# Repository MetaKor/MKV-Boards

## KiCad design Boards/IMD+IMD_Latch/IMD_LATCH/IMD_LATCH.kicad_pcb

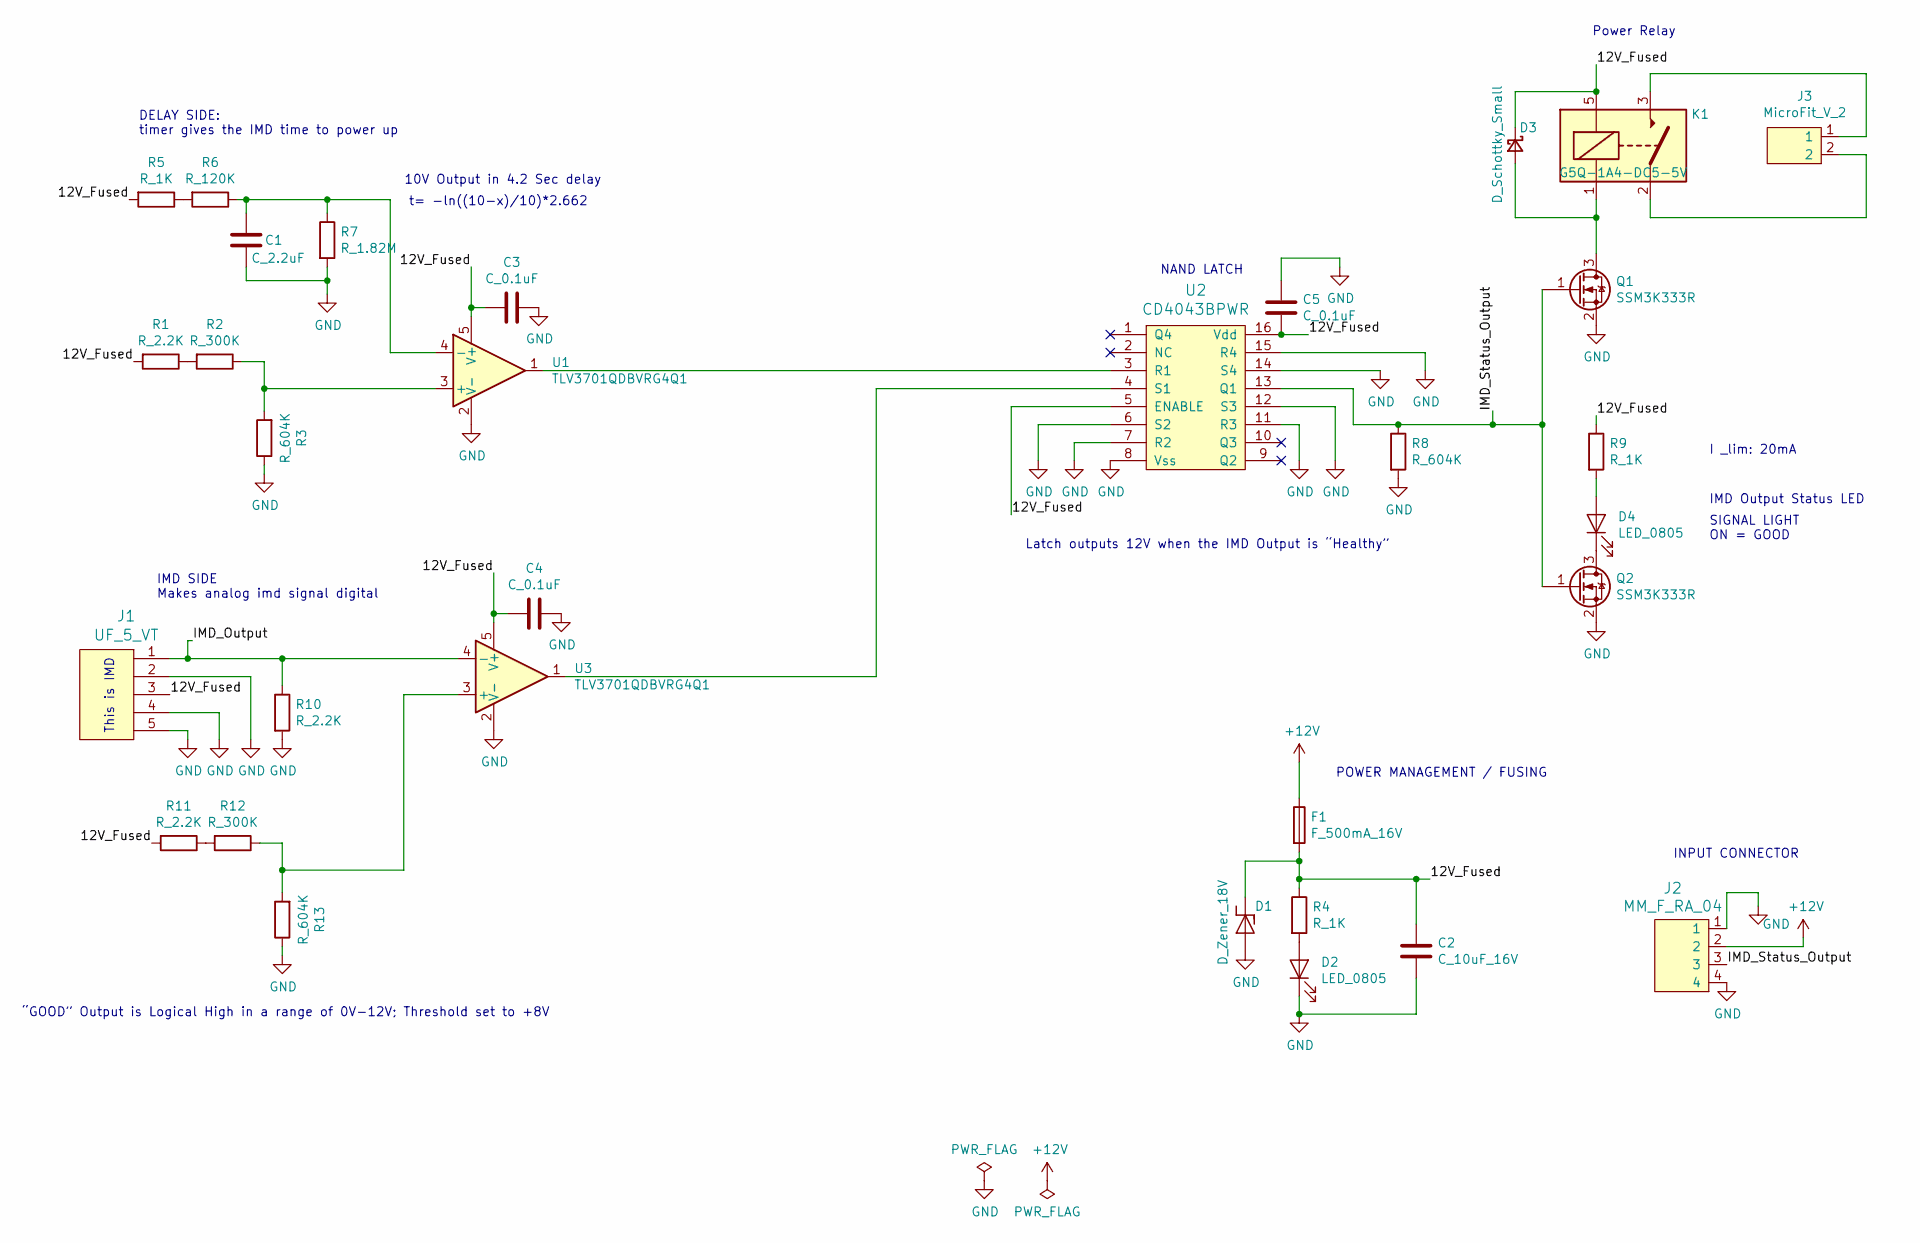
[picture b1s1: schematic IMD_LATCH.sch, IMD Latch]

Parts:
C1: C_2.2uF; C_0603_1608Metric; MPN 311-1451-1-ND
C2: C_10uF_16V; C_0805_OEM; MPN 1276-2399-1-ND
C3, C4, C5: C_0.1uF; C_0805_OEM; MPN 478-3352-1-ND
D1: D_Zener_18V; DO-214AA; MPN SMBJ5355B-TPMSCT-ND
D2, D4: LED_0805; LED_0805_OEM; MPN 475-1410-1-ND
D3: D_Schottky_Small; D_0805_OEM
F1: F_500mA_16V; Fuse_1210; MPN 507-1786-1-ND
J1: UF_5_VT; Ultrafit_5; MPN WM11667-ND
J2: MM_F_RA_04; micromatch_female_ra_4; MPN 338070-4
J3: MicroFit_V_2; MPN WM10660-ND
K1: G5Q-1A4-DC5-5V; Relay_SPST_OMRON-G5Q-1A4_OEM; MPN Z3632-ND
Q1, Q2: SSM3K333R; SOT-23F; MPN SSM3K333RLFCT-ND
R1, R10, R11: R_2.2K; R_0805_OEM; MPN RMCF0805FT2K20CT-ND
R2, R12: R_300K; R_0805_OEM; MPN P300KDACT-ND
R3, R8, R13: R_604K; R_0805_OEM; MPN RMCF0805FT604KCT-ND
R4, R5, R9: R_1K; R_0805_OEM; MPN RNCP0805FTD1K00CT-ND
R6: R_120K; R_0805_OEM; MPN RMCF0805FT120KCT-ND
R7: R_1.82M; R_0805_OEM; MPN RMCF0805FT1M82CT-ND
U1, U3: TLV3701QDBVRG4Q1; SOT-23-5_OEM; MPN 497-10249-1-ND
U2: CD4043BPWR; TSSOP-16-OEM; MPN 296-14106-1-ND

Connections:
+12V: F1.1, J2.2
/12V_Fused: C2.1, C3.2, C4.2, C5.2, D1.1 (K), D3.1 (K), F1.2, J1.3, K1.5, R1.2, R4.1, R5.2, R9.1, R11.2, U1.5 (V+), U2.5 (ENABLE), U2.16 (Vdd), U3.5 (V+)
/IMD_Output: J1.1, R10.1, U3.4 (-)
/IMD_Status_Output: J2.3, Q1.1 (G), Q2.1 (G), R8.1, U2.13 (Q1)
GND: C1.2, C2.2, C3.1, C4.1, C5.1, D1.2 (A), D2.1 (K), J1.2, J1.4, J1.5, J2.1, J2.4, Q1.2 (S), Q2.2 (S), R3.1, R7.2, R8.2, R10.2, R13.1, U1.2 (V-), U2.6 (S2), U2.7 (R2), U2.8 (Vss), U2.11 (R3), U2.12 (S3), U2.14 (S4), U2.15 (R4), U3.2 (V-)
unnamed: C1.1, R6.1, R7.1, U1.4 (-)
unnamed: D2.2 (A), R4.2
unnamed: D3.2 (A), K1.1, Q1.3 (D)
unnamed: D4.1 (K), Q2.3 (D)
unnamed: D4.2 (A), R9.2
unnamed: J3.1, K1.3
unnamed: J3.2, K1.2
unnamed: R1.1, R2.2
unnamed: R2.1, R3.2, U1.3 (+)
unnamed: R5.1, R6.2
unnamed: R11.1, R12.2
unnamed: R12.1, R13.2, U3.3 (+)
unnamed: U1.1, U2.3 (R1)
unnamed: U2.4 (S1), U3.1

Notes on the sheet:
IMD SIDE Makes analog imd signal digital
“GOOD” Output is Logical High in a range of 0V-12V; Threshold set to +8V
INPUT CONNECTOR
NAND LATCH
Power Relay
10V Output in 4.2 Sec delay
t= -ln((10-x)/10)*2.662
DELAY SIDE: timer gives the IMD time to power up
This is IMD
Latch outputs 12V when the IMD Output is “Healthy”
POWER MANAGEMENT / FUSING
SIGNAL LIGHT ON = GOOD
I _lim: 20mA
IMD Output Status LED

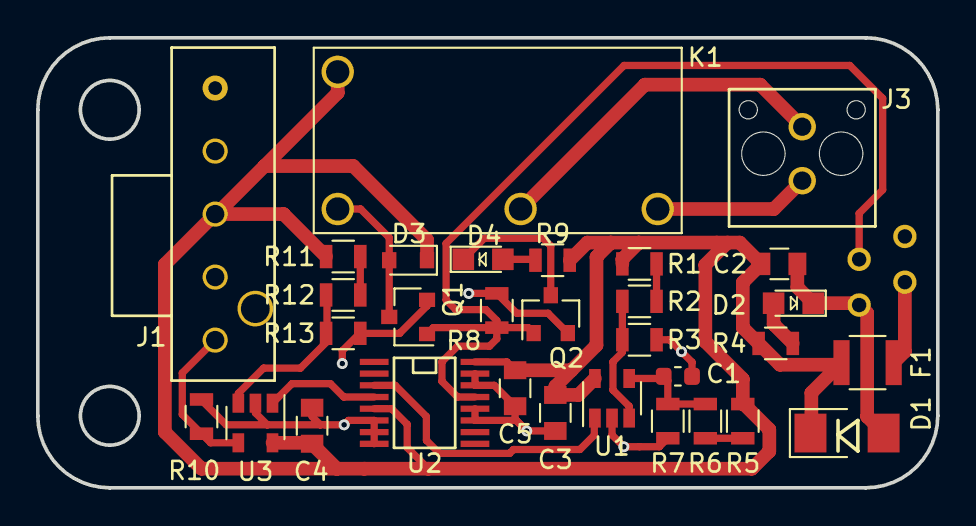
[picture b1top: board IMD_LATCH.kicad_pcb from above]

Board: 2 copper layers, 50.0 x 25.0 mm, 32 parts (1 on the bottom side), 19 nets.

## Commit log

2020-11-22 Primary detangling of IMD Latch layout ratsnest
2020-11-22 First draft of complete layout
2020-12-04 Layout revision with updated connector placement and back layer.
